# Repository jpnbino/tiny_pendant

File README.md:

# TINY PENDANT #

Tiny pendant is little beautiful project you can wear and shine.

The reason this project was to give an introduction to PCB Design to some newcomers in the area. Therefore, it was a fun hands-on lab.

## Version

    v1.0 - Initial version

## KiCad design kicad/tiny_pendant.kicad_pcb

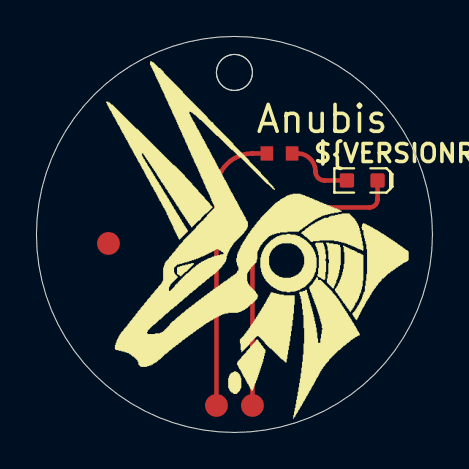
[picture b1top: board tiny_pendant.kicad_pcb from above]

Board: 2 copper layers, 22.0 x 22.0 mm, 6 parts (0 on the bottom side), 3 nets.

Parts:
FID1: FIDUCIAL; FIDUCIAL - 1.27mm
H1: HANGING_HOLE_2MM
J1, J2: 1.27mm; SOLDER PAD - 1.27mm
LED1: RED; LED-0603-RED
R1: 1k; RESC1608X06N

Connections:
GND: J2.1, LED1.K
unnamed: LED1.A, R1.1
VCC_5V: J1.1, R1.2

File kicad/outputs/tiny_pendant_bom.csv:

"Reference","Value","Footprint","QUANTITY"
"FID1","FIDUCIAL","tiny_pendant:FIDUCIAL - 1.27mm","1"
"J1,J2","1.27mm","tiny_pendant:SOLDER PAD - 1.27mm","2"
"LED1","RED","tiny_pendant:LED-0603-RED","1"
"PCB1","Tiny_Pendant_V1I1","","1"
"R1","1k","tiny_pendant:RESC1608X06N","1"

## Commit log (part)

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2017-06-29 README.md created online with Bitbucket
2022-06-20 release v1.0
